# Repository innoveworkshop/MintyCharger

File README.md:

# MintyCharger

A complete USB-powered PP3 battery charger that fits neatly inside an Altoids
tin. To learn more please [visit the project website](https://innoveworkshop.com/product/mintycharger).

## Supported Batteries

This charger is capable of working with the following battery chemistries and
nominal voltages:

  - NiMH
    - 9.6V
	- 8.4V
	- 7.2V
  - Lithium
    - 7.4V

## Board Layout

## License

<br />This work is licensed under a <a rel="license" href="http://creativecommons.org/licenses/by-nc-sa/4.0/">Creative Commons Attribution-NonCommercial-ShareAlike 4.0 International License</a>.

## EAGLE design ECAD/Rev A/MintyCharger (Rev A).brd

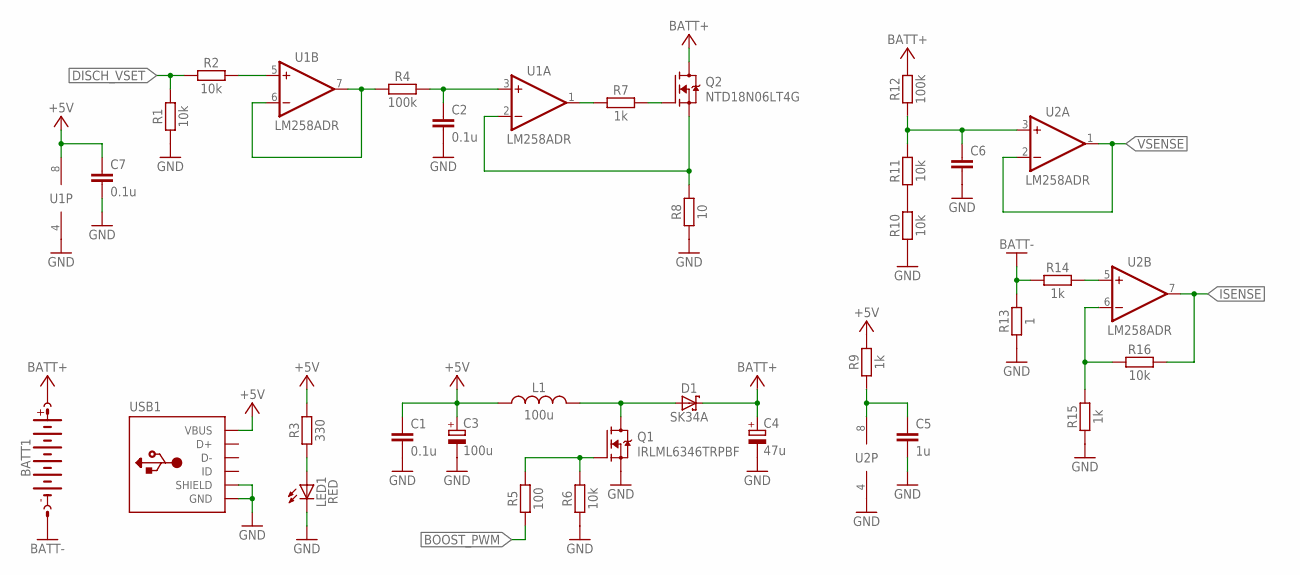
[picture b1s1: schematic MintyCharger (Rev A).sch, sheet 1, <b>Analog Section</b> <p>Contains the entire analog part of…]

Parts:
BATT1: KEYSTONE-590-9V
C1, C2, C7: 0.1u; C0805
C3: 100u; PANASONIC_D
C4: 47u; PANASONIC_C
C5: 1u; C0805
C6: C0805
D1: SK34A; SMA
L1: 100u; ELLCTP
LED1: RED; CHIP-LED0805
Q1: IRLML6346TRPBF; SOT23
Q2: NTD18N06LT4G; TO252
R1, R2, R6, R10, R11, R16: 10k; R0805
R3: 330; R0805
R4, R12: 100k; R0805
R5: 100; R0805
R7, R9, R14, R15: 1k; R0805
R8: 10; R1206
R13: 1; R1206
U1, U2: LM258ADR; SO08
USB1: USB-MICRO-10118194-0001LF; AMPHENOL_10118194-0001LF

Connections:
+5V: C1.1, C3.+, C7.1, L1.P$1 (1), R3.2, R9.2, U1.8 (V+), USB1.VCC (VBUS); also elsewhere on the board
BATT+: BATT1.P$+1 (+), BATT1.P$+2 (+), BATT1.P$+3 (+), C4.+, D1.C, Q2.3 (D), R12.2
BATT-: BATT1.P$-1 (-), BATT1.P$-2 (-), BATT1.P$-3 (-), R13.2, R14.1
BOOST_PWM: R5.1; also elsewhere on the board
DISCH_VSET: R1.2, R2.1; also elsewhere on the board
GND: C1.2, C2.2, C3.-, C4.-, C5.2, C6.2, C7.2, LED1.C, Q1.2 (S), R1.1, R6.1, R8.1, R10.1, R13.1, R15.1, U1.4 (V-), U2.4 (V-), USB1.GND, USB1.S1 (SHIELD), USB1.S2 (SHIELD), USB1.S3 (SHIELD), USB1.S4 (SHIELD), USB1.S5 (SHIELD), USB1.S6 (SHIELD), USB1.S7 (SHIELD), USB1.S8 (SHIELD); also elsewhere on the board
ISENSE: R16.2, U2.7 (OUT); also elsewhere on the board
unnamed: R10.2, R11.1
unnamed: C6.1, R11.2, R12.1, U2.3 (+IN)
unnamed: R15.2, R16.1, U2.6 (-IN)
unnamed: Q2.2 (S), R8.2, U1.2 (-IN)
unnamed: C2.1, R4.2, U1.3 (+IN)
unnamed: R4.1, U1.6 (-IN), U1.7 (OUT)
unnamed: R2.2, U1.5 (+IN)
unnamed: Q2.1 (G), R7.2
unnamed: R7.1, U1.1 (OUT)
unnamed: R14.2, U2.5 (+IN)
unnamed: C5.1, R9.1, U2.8 (V+)
unnamed: D1.A, L1.P$2 (2), Q1.3 (D)
unnamed: Q1.1 (G), R5.2, R6.2
unnamed: LED1.A, R3.1
VSENSE: U2.1 (OUT), U2.2 (-IN); also elsewhere on the board

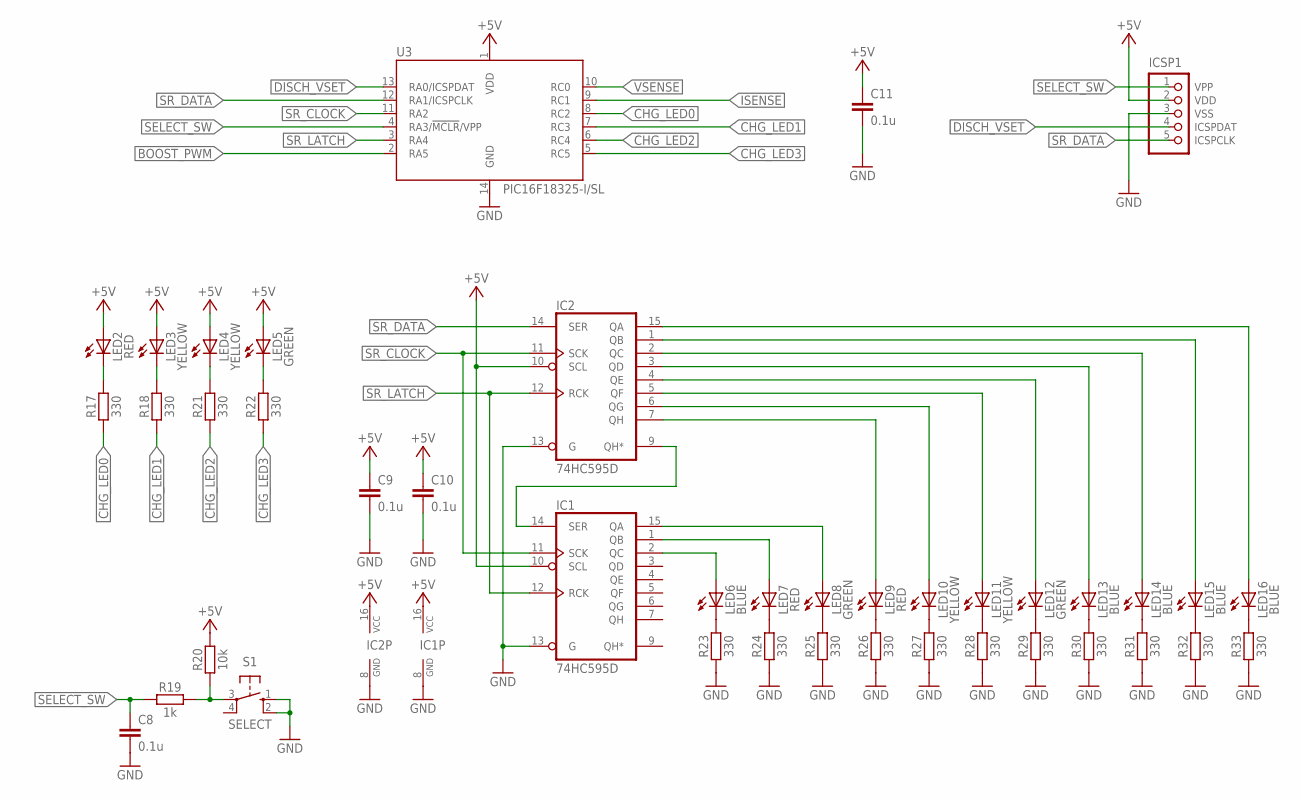
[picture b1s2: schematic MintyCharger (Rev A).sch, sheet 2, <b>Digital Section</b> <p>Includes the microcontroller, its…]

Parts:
C8, C9, C10, C11: 0.1u; C0805
IC1, IC2: 74HC595D; SO16
ICSP1: PIC-ICSPJST-XH; B5B-XH-A
LED2, LED7, LED9: RED; CHIP-LED0805
LED3, LED4, LED10, LED11: YELLOW; CHIP-LED0805
LED5, LED8, LED12: GREEN; CHIP-LED0805
LED6, LED13, LED14, LED15, LED16: BLUE; CHIP-LED0805
R17, R18, R21, R22, R23, R24, R25, R26, R27, R28, R29, R30, R31, R32, R33: 330; R0805
R19: 1k; R0805
R20: 10k; R0805
S1: SELECT; PTS645-SMT
U3: PIC16F18325-I/SL; SO14

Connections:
+5V: C9.1, C10.1, C11.1, IC1.10 (SCL), IC1.16 (VCC), IC2.10 (SCL), IC2.16 (VCC), ICSP1.2 (VDD), LED2.A, LED3.A, LED4.A, LED5.A, R20.2, U3.1 (VDD); also elsewhere on the board
BOOST_PWM: U3.2 (RA5); also elsewhere on the board
CHG_LED0: R17.1, U3.8 (RC2)
CHG_LED1: R18.1, U3.7 (RC3)
CHG_LED2: R21.1, U3.6 (RC4)
CHG_LED3: R22.1, U3.5 (RC5)
DISCH_VSET: ICSP1.4 (ICSPDAT), U3.13 (RA0/ICSPDAT); also elsewhere on the board
GND: C8.2, C9.2, C10.2, C11.2, IC1.8 (GND), IC1.13 (G), IC2.8 (GND), IC2.13 (G), ICSP1.3 (VSS), R23.1, R24.1, R25.1, R26.1, R27.1, R28.1, R29.1, R30.1, R31.1, R32.1, R33.1, S1.1 (S), S1.2 (S1), U3.14 (GND); also elsewhere on the board
ISENSE: U3.9 (RC1); also elsewhere on the board
unnamed: LED5.C, R22.2
unnamed: LED4.C, R21.2
unnamed: LED3.C, R18.2
unnamed: LED2.C, R17.2
unnamed: IC1.14 (SER), IC2.9 (QH*)
unnamed: LED9.C, R26.2
unnamed: LED10.C, R27.2
unnamed: LED11.C, R28.2
unnamed: LED12.C, R29.2
unnamed: LED13.C, R30.2
unnamed: LED14.C, R31.2
unnamed: LED15.C, R32.2
unnamed: LED16.C, R33.2
unnamed: R19.2, R20.1, S1.3
unnamed: LED6.C, R23.2
unnamed: LED7.C, R24.2
unnamed: LED8.C, R25.2
unnamed: IC1.15 (QA), LED8.A
unnamed: IC1.1 (QB), LED7.A
unnamed: IC1.2 (QC), LED6.A
unnamed: IC2.7 (QH), LED9.A
unnamed: IC2.6 (QG), LED10.A
unnamed: IC2.5 (QF), LED11.A
unnamed: IC2.4 (QE), LED12.A
unnamed: IC2.3 (QD), LED13.A
unnamed: IC2.2 (QC), LED14.A
unnamed: IC2.1 (QB), LED15.A
unnamed: IC2.15 (QA), LED16.A
SELECT_SW: C8.1, ICSP1.1 (VPP), R19.1, U3.4 (RA3/!MCLR!/VPP)
SR_CLOCK: IC1.11 (SCK), IC2.11 (SCK), U3.11 (RA2)
SR_DATA: IC2.14 (SER), ICSP1.5 (ICSPCLK), U3.12 (RA1/ICSPCLK)
SR_LATCH: IC1.12 (RCK), IC2.12 (RCK), U3.3 (RA4)
VSENSE: U3.10 (RC0); also elsewhere on the board

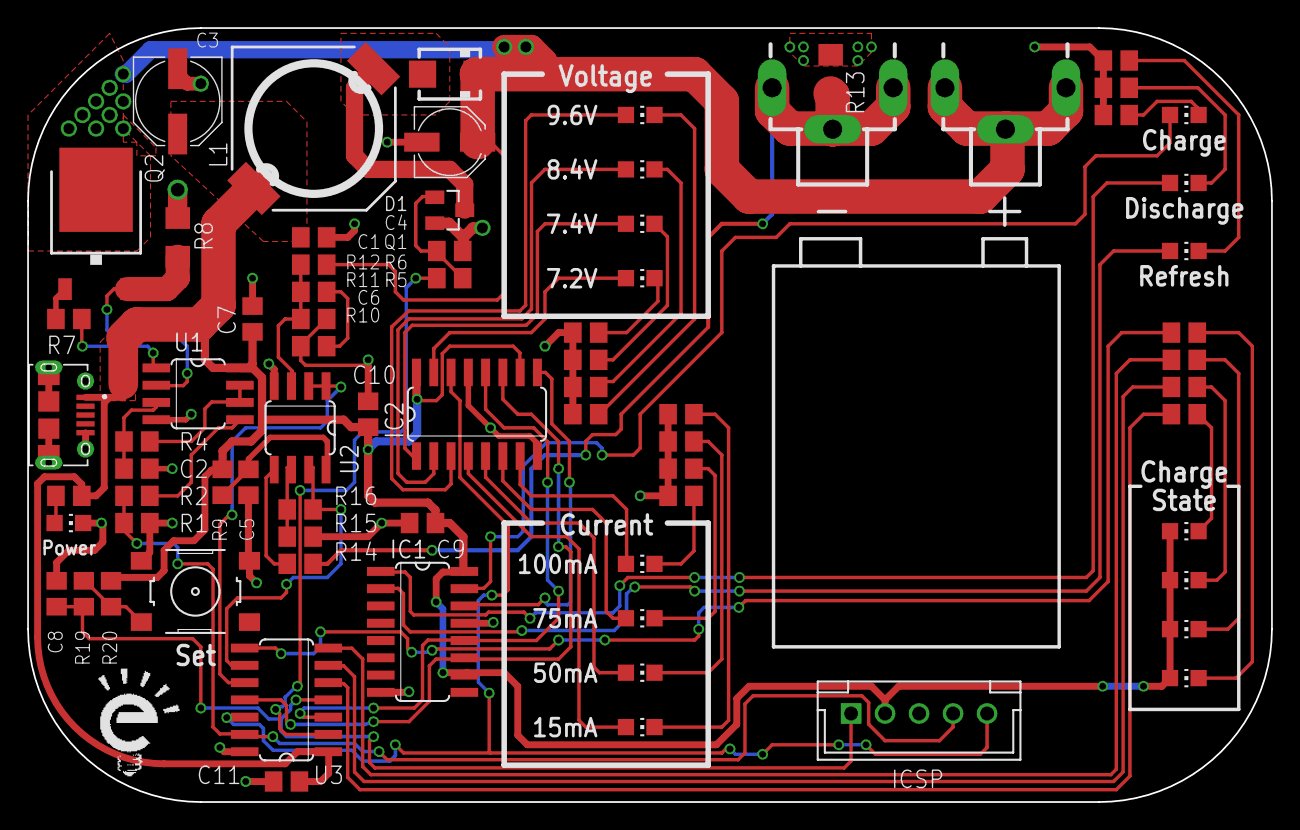
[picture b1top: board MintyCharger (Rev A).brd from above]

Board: 2 copper layers, 91.4 x 56.9 mm, 74 parts (0 on the bottom side), 58 nets.

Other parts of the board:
U$1: ALTOIDSTIN-DIM

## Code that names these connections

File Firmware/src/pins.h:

/* 
 * pins.h
 * Pin definitions.
 * 
 * @author Nathan Campos <nathan@innoveworkshop.com>
 */

#ifndef PINS_H
#define	PINS_H

//                           16F18325
//                         +----------+
// LED Shift Register DAT -|RA0    RC0|- Voltage Sense - ANC0
// LED Shift Register CLK -|RA1    RC1|- Current Sense - ANC1
// LED Shift Register LAT -|RA2    RC2|- Charge LED 0
// Select Switch          -|RA3    RC3|- Charge LED 1
// Discharge Enable       -|RA4    RC4|- Charge LED 2
// Boost DC/DC PWM - PWM1 -|RA5    RC5|- Charge LED 3
//                         +----------+


// Pin definitions.
#define DISCH_VSET 1         // RA0
#define SR_DATA    (1 << 1)  // RA1
#define SR_CLOCK   (1 << 2)  // RA2
#define BTN_SELECT (1 << 3)  // RA3
#define SR_LATCH   (1 << 4)  // RA4
#define BOOST_PWM  (1 << 5)  // RA5
#define VSENSE     1         // RC0
#define ISENSE     (1 << 1)  // RC1
#define CHG_LED0   (1 << 2)  // RC2
#define CHG_LED1   (1 << 3)  // RC3
#define CHG_LED2   (1 << 4)  // RC4
#define CHG_LED3   (1 << 5)  // RC5

// Analog channel definitions.
#define ADC_CH_VSENSE 0b10000
#define ADC_CH_ISENSE 0b10001

#endif	/* PINS_H */

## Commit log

2020-06-18 Added a license
2020-06-18 Added the license to the README
2020-06-18 Added an empty MPLAB X project
2020-06-18 Minor typo
2020-08-01 Created a simple home-etched PCB prototype to start working on the firmware
2020-08-01 Setup the programmer
2020-08-01 Put up some scaffolding
2020-08-01 Defined the pins
2020-08-01 Added the clock frequency to the configurations header so that it can be used by timer functions
2020-08-01 Added the simulations directory to the ignore list
2020-08-01 Setting up the digital I/O pins
2020-08-01 Everything more or less setup to a 'working' degree
2020-08-02 Organized all the voltage regulation stuff
2020-08-02 Current regulation added
2020-08-02 Measuring the battery voltage in a differential manner
2020-08-02 Added some functions to get the battery voltage and current as floats
2020-08-03 Disabled PPS1WAY
2020-08-03 Added serial communication to aid in debugging
2020-08-03 Added integer conversion serial functions
2020-08-03 Some simple debugging
2020-08-03 Fixed the battery measurement and improved the output regulation
2020-08-03 Removed all the debugging stuff
2020-08-03 Added the ability to start and stop the voltage regulator
2020-08-03 Organized alll the source files into their own folder
2020-08-03 Started working on the user interface part
2020-08-04 Minor repositioning of a GND point
2020-08-04 Finished the prototype shift register module schematic
2020-08-04 Renumbered the shift register prototype module RefDes
2020-08-04 Finished the shift register prototype module PCB
2020-08-04 Added shift register prototype laser etch PDFs
2020-08-05 Moved the pin mapping graphics to the appropriate header file
2020-08-05 Started working on getting the shift register to work
2020-08-05 Removed all the MSSP code that didn't work as expected
2020-08-05 Setting the LEDs according to the selected settings
2020-08-06 Detecting a button hold
2020-08-06 Started working on the selection mode
2020-08-06 Handling selection changes
2020-08-06 Put on a little show upon reset
2020-08-06 Blinkenlights to indicate a configuration selection
2020-08-10 Finished the Rev A schematic
2020-08-12 Finished the board layout of RevA
2020-08-12 Ignoring the CAM directory
2020-08-12 Added more battery types to the README
2021-04-06 Moved all the firmware code to a new directory and made the pre-prototype code work in the Rev A board
2021-04-06 ECAD - Minor changes to the Rev A files
2021-04-07 Firmware - Exposing a bit of the state of the UI to other modules
    Ref T35
2021-04-07 Firmware - Detecting end-of-charge and exposing a whole bunch of states from the voltage regulator module
    Ref T35
2021-04-07 Firmware - Created a function to get the battery cell voltage Ref T35
2021-04-07 Firmware - Displaying a charge state gauge Ref T35
2021-04-08 Removed the serial debug source files since they are useless now
2021-04-08 Fixed the bug where GetBatteryVoltage always returned 0
    Fixes T37
2021-04-08 Fixed the way the battery voltage was calculated
2021-04-08 Firmware - Blinking to indicate the current charging state
    Ref T35
2021-04-08 Firmware - Changed the voltage regulation algorithm a bit
2021-04-08 Firmware - Fixed the indentation of the whole project
2021-04-08 Firmware - Detecting battery disconnection
    Ref T38
2021-04-09 Firmware - Trying (and failling) to detect the insertion of a battery
    Ref T38
2021-04-09 Firmware - Removed the battery insertion detection function
    Ref T38
2021-04-09 Firmware - Minor change to the way the battery gauge is calculated
    Ref T35 T38
2021-04-09 Firmware - Start charging by clicking the select button
    Ref T38
2021-04-09 Firmware - Detecting the end of a charge
    Ref T38
2021-04-09 Firmware - Forgot to remove a statement
2021-04-10 Firmware - Comitting configuration changes to the voltage regulator
    Ref T42
2021-04-10 Firmware - Making sure the gauge is blank while selecting a configuration
    Fixes T43
2021-04-10 Firmware - Fixed the charging current setting values
    Ref T42
2021-04-10 Firmware - Minor changes to the project settings
2021-04-10 Firmware - Fixed the way the configuration LEDs were being set
    Fixes T44
2021-04-12 Firmware - Implemented abstration methods to deal with the EEPROM
    Ref T41
2021-04-12 Firmware - Loading configurations from the EEPROM
    Ref T41
2021-04-12 Firmware - Saving configuration to EEPROM
    Fixes T41, T42
2021-04-12 Firmware - Start charging as soon as the user finishes setting up the configuration
2021-04-12 Firmware - Converted spaces to tabs (MPLAB X reset for some reason)
2021-04-12 Firmware - Added a whole bunch of 'inline' function optiomazations
2021-04-12 Firmware - Minor change to the slew rate of the PWM pin
2021-04-13 Firmware - Started working in the scaffolding of the electronic load
    Ref T39
2021-04-13 Firmware - Fixed the project source file locations
2021-04-13 Firmware - Improved end of charge detection by getting the mean current
2021-04-13 Firmware - Changed the number of current mean cycles
2021-04-13 Firmware - Setting the electronic load current and enabling/disabling it
    Ref T39
2021-04-13 Firmware - Implemented the load in the interface and fixed a little bug in the configuration selection
    Ref T39
2021-04-13 Firmware - Minor change
2021-04-13 Firmware - Fixed an include
2021-04-13 Firmware - Reorganized all of the ADC-related stuff into its own module
    Ref T39, T35
2021-04-14 Firmware - Moved to the PRO version of XC8
2021-04-14 Firmware - Fixed a stack overflow warning
    Apparently XC8 isn't inlining my functions.
2021-04-14 Firmware - Fixed a bug where the regulators and the load would be active together
    Apparently you can't have source file global variables with the same
    name in another source file.
    Fixes T47
    Ref T39
2021-04-14 Firmware - Implemented the electronic load voltage cutoff detection
    Ref T39
2021-04-14 Firmware - Greatly improved the battery gauge
    Fixes T48, T39
2021-04-16 Firmware - Started implementing battery refreshing
    Ref T40
2021-04-16 Firmware - Showing the current cycle of a battery refresh
    Ref T40
2021-04-16 Firmware - Corrected a couple of typos
2021-04-16 Firmware - Fixed a stack overflow caused by the refresh routines
    Fixes T40
2021-04-16 Firmware - Changed VSENSE_VDIV to be a fixed number
2021-04-16 Firmware - Enabled optimizations
2021-04-17 Firmware - Indented setup comments
2021-04-17 Firmware - Fixed some typos
2021-04-17 Firmware - More minor changes to indentation
2021-04-17 Firmware - Decreased the gauge LED flashing frequency
    Fixes T50
2021-04-17 Firmware - Implemented a way to know the version of the firmware
    Fixes T45
2021-04-17 Firmware - Clearing a compiler warning about implicit type conversions
2021-04-17 Firmware - Enabled the watchdog timer
    Fixes T36
2021-04-23 Added an image to the README
    Fixes T54
2021-04-23 Added the project logo to the README
    Ref T54
2021-04-23 Fixed the project logo in the README
    Ref T54
2021-05-07 Fixed a bug where the shift registers would get out of sync on startup
    Fixes T52
